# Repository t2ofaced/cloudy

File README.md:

# cloudy

A custom designed 60% Keyboard this keyboard is the first diy / electronic project i made from scratch, so idea was simple i wanted a keyboard so i desigined one now hopefully i can assemble it too so this keyboard use nice nano v2 clone pro micro nrf52840 development board as it give me freedom of wireless kayboard this keyboard also includes 1 enoder and 1 display and it is fully rgb thanks to SK6812MINI-E SMD leds

OnShape Link- https://cad.onshape.com/documents/02d1cc1f7ec3e59871e42e68/w/e27206701595b8be94d4fc96/e/017436c4cffd3847ba6185ca

---

## Schematics & Circuitry

Electornic part of this Proj is desigined in KiCad 10.0

<br>
this is main circuitry 

<br>

<br>
keyswitch matrix

<br>

<br>
rgb chain

---

## PCB Routing & 3D View

<br>
routed pcb

<br>

<br>
3d view

---

## CAD & Case Design

Mechanical part / CAD is desigined in 4 parts 2 each for Top plate and Base plate it is in 4 parts so  that it can be printed easily
Onshape - https://cad.onshape.com/documents/02d1cc1f7ec3e59871e42e68/w/e27206701595b8be94d4fc96/e/d50220b72c1b89afdf243eaf

<br>
keyboard with base plate

<br>

<br>
keyboard with top plate

---

## Final Assembly

<br>
fully assembled

# Bill of Materials

| Part Name | Quantity | Link | Info | Price (USD) |
|---|---|---|---|---|
| JLCPCB PCB Manufacturing & Shipping | 1 | [Link](https://jlcpcb.com/) | PCB | $35 |
| 0.96 inch OLED Display | 1 | [Link](https://robu.in/product/0-96-oled-display-module/) | OLED display | $2.35 |
| Tactile Switches | 7 sets | [Link](https://meckeys.com/shop/accessories/keyboard-accessories/key-switches/cherry-mx-rgb-switch/) | Switches | $26.3 |
| NiceNanoV2 | 1 | [Link](https://robu.in/product/pro-micro-nrf52840-development-board-compatible-with-nicenano-v2-0/) | MCU | i will buy my owm ($8.67) |
| 1N4148 Diodes | 70 | [Link](https://quartzcomponents.com/products/1n4148-zener-diodel) | Diodes | $2.22 |
| Custom Keycaps | 1 | [Link](https://curiositycaps.in/products/comic-mixed-light-cherry-1-7mm-thick-pbt-keycaps) | Keycaps | $24.35 |
| SK6812MINI-E SMD | 72 | [Link](https://www.etstore.in/products/e9974?variant=48993209319675&country=IN&currency=INR) | RGB LEDs | $9.73 |
| LiPo Battery | 1 | [Link](https://robu.in/product/400mah-pcm-protected-micro-li-po-battery/) | 3.7V 400mAh 1S | $2.32 |
| Disc Capacitor | 70 | [Link](https://robu.in/product/100nf-50v-disc-capacitor/) | 100nF 50V | $1 |
| Aluminum Electrolytic Capacitors | 5 | [Link](https://robu.in/product/ers1am471e12ot-aishi-470uf-10v-%C2%B120-plugind6-3xl12mm-aluminum-electrolytic-capacitors-leaded-rohs/?gad_source=1&gad_campaignid=17427802703&gbraid=0AAAAADvLFWeqncwaNG3o_D6R6zCnwtxQC) | ERS1AM471E12OT-AISHI 470uF 10V ±20% Plugin | $0.5 |
| Resistor 470 Ohms | 10 | [Link](https://www.ktron.in/product/resistor-470-ohms-0-25w-5-th/) | 470 Ohms 0.25W 5% TH | $0.2 |
| Male Connector | 3 | [Link](https://robu.in/product/ph-aw-2mm-2-pin-wafer-male-connector-through-hole-right-angle/) | PH-AW 2mm 2 pin | $0.2 |
| Rotary Encoder with Switch | 1 | [Link](https://robu.in/product/hongyan-ec11h-7ce20p1zd20-rotary-encoder-with-push-button-switch-vertical-plug-in-5-pin/) | EC11H 7CE20P1ZD20 5-Pin | $0.7 |
| Slide Switch | 5 | [Link](https://robu.in/product/slide-switch-ss-12d07-1p2t/) | SS-12D07 1P2T | $0.2 |
| Tactile Switch | 5 | [Link](https://robu.in/product/ws-a06-4-3-waterproof-tact-switch-4-pin6x6x4-3/) | 6x6x4.3mm 4 Pin | $0.2 |
| Stabilizers | 5 | [Link](https://stackskb.com/store/durock-clear-screw-in-stabilizers-v2) | 4+1 set | $16.93 |
| **TOTAL** | | | | **~$124** |

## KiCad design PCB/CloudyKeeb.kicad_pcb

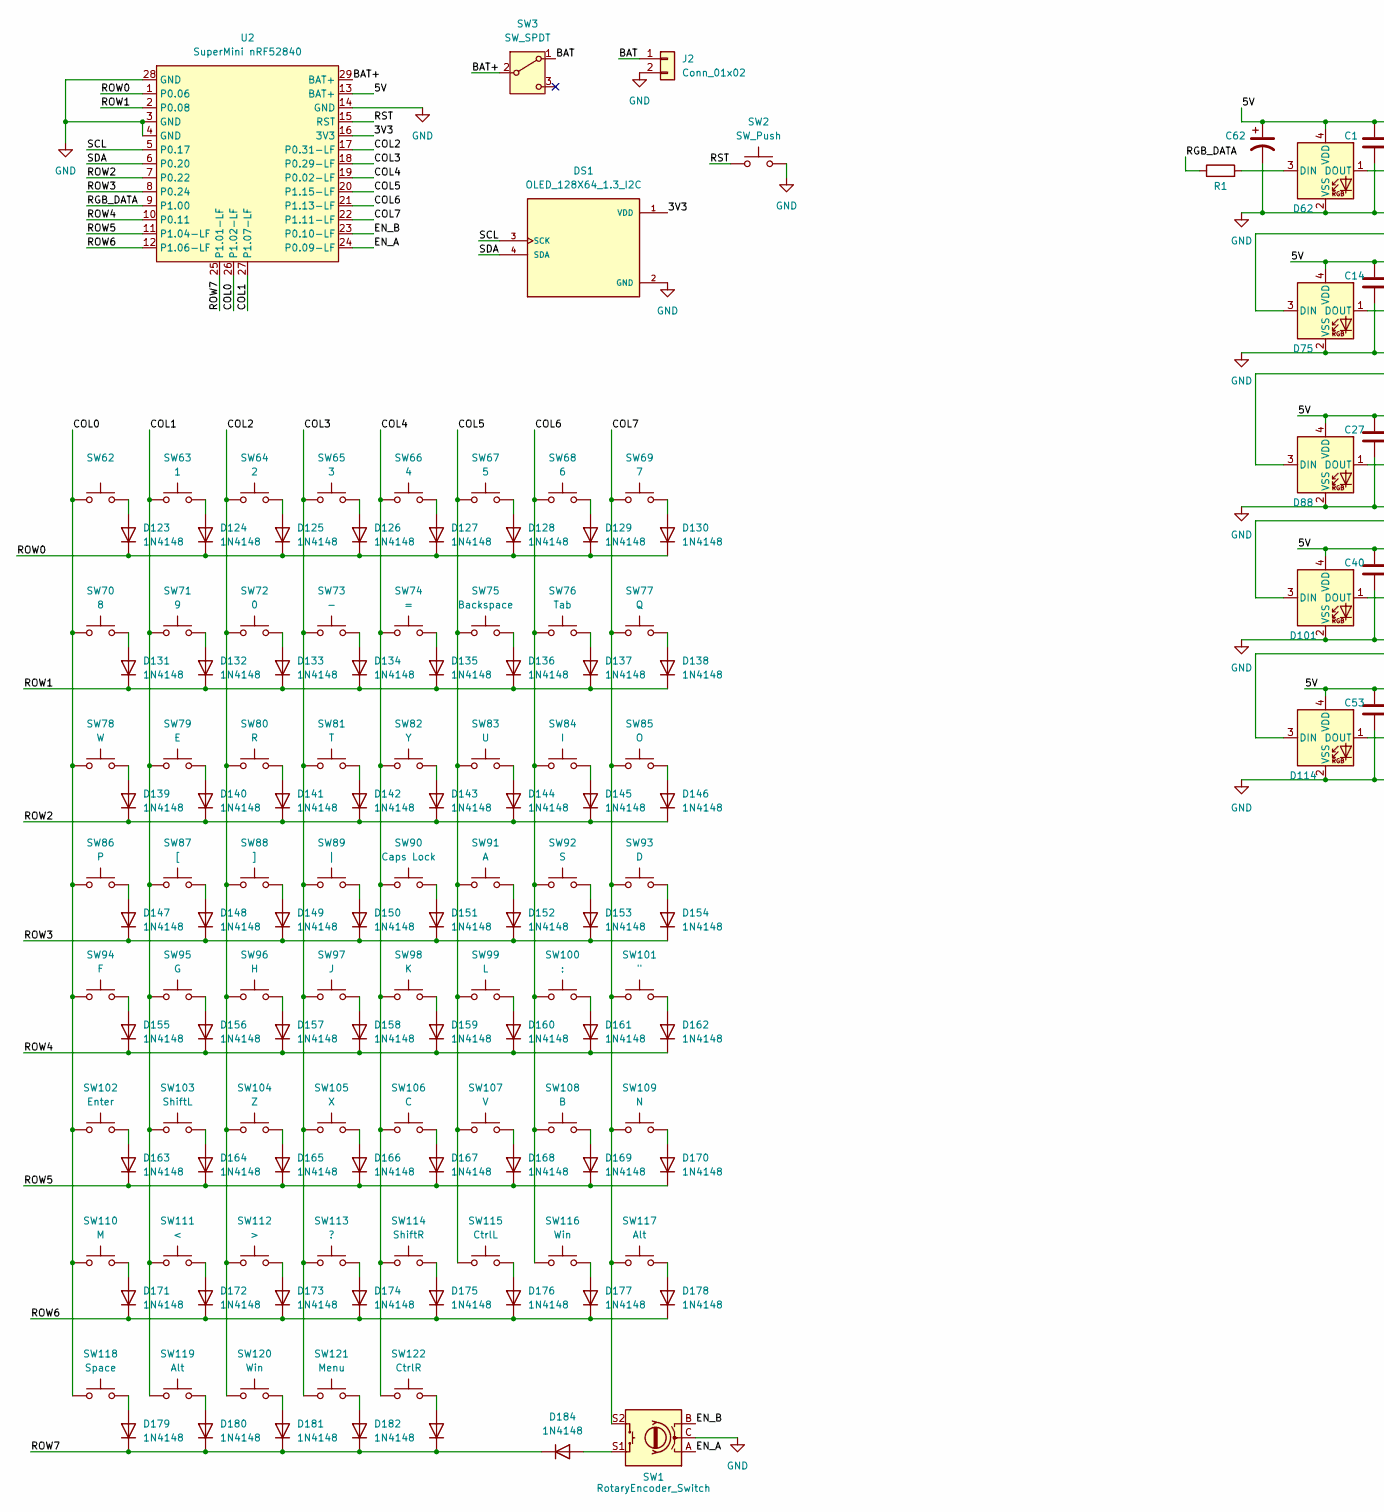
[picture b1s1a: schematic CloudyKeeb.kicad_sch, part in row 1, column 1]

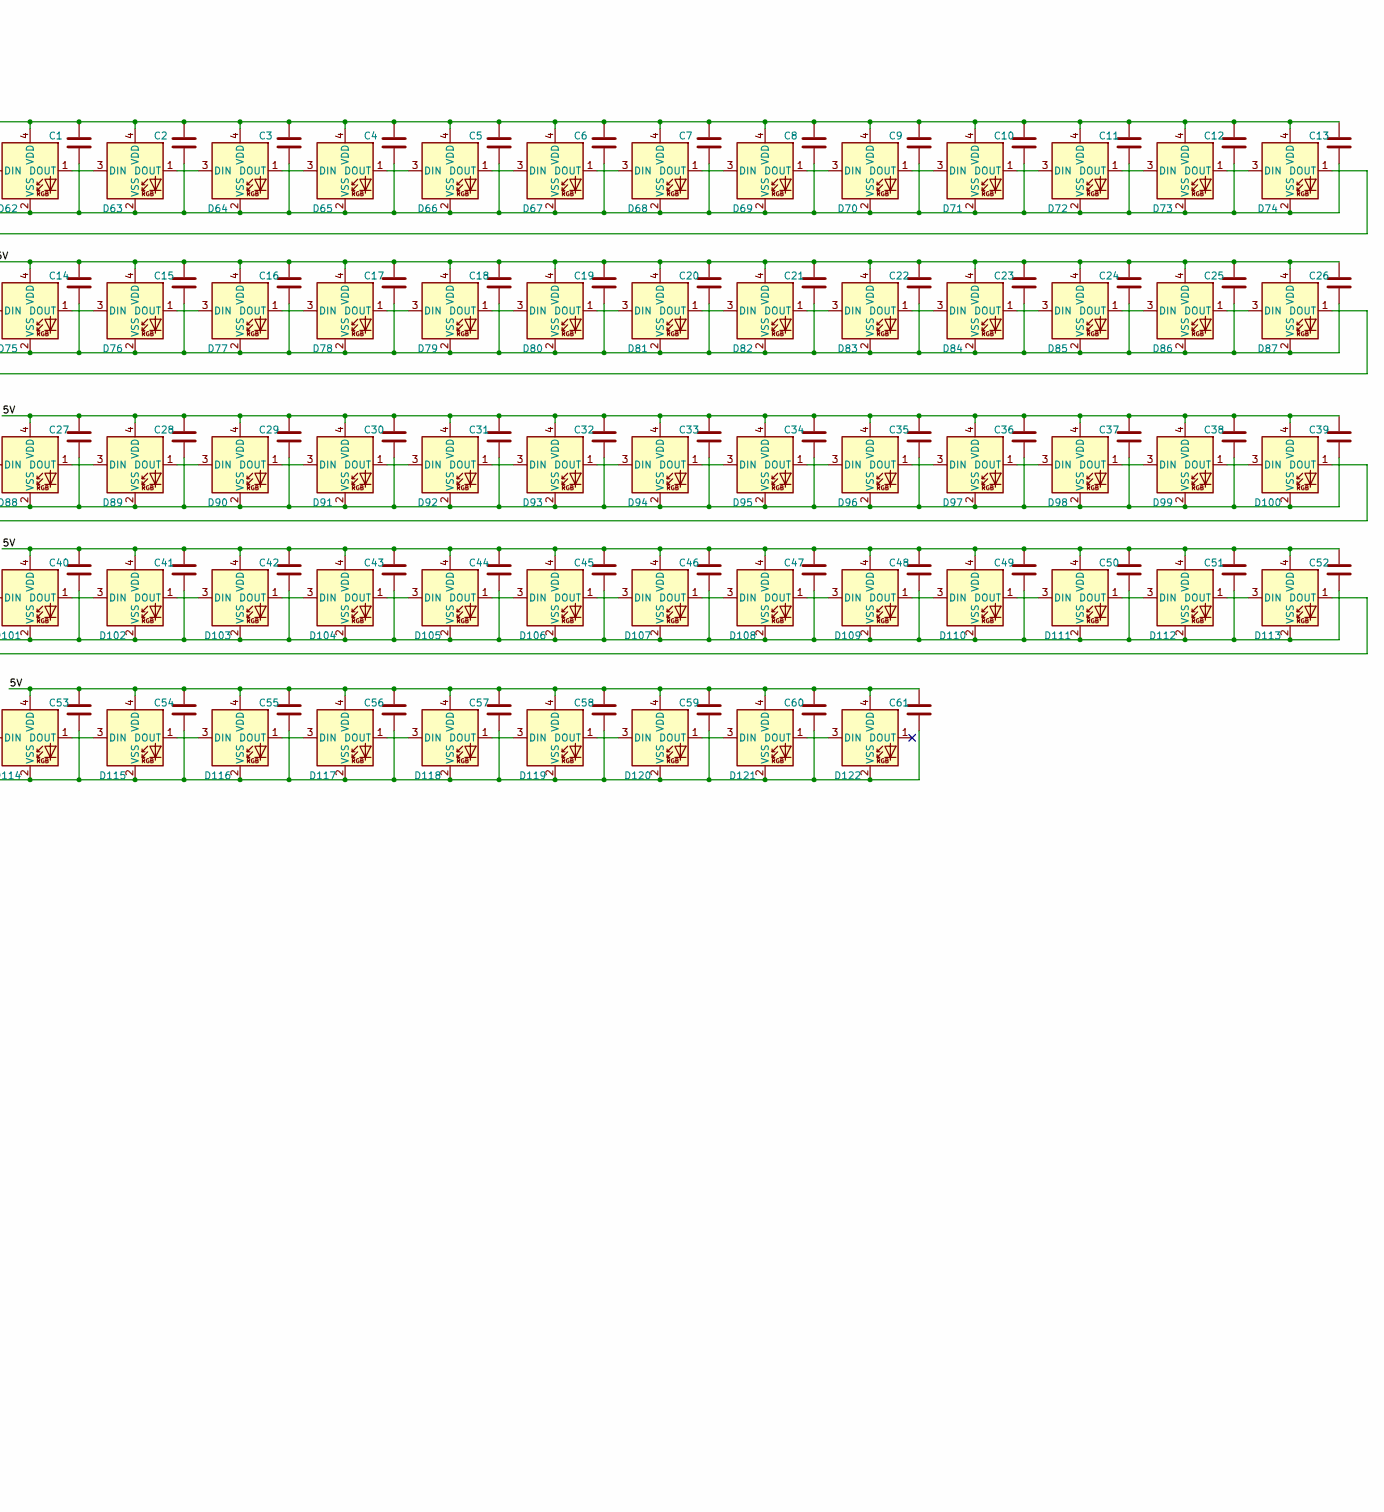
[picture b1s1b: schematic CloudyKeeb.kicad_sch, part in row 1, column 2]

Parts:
C1, C2, C3, C4, C5, C6, C7, C8, C9, C10, C11, C12, C13, C14, C15, C16, C17, C18, C19, C20, C21, C22, C23, C24, C25, C26, C27, C28, C29, C30, C31, C32, C33, C34, C35, C36, C37, C38, C39, C40, C41, C42, C43, C44, C45, C46, C47, C48, C49, C50, C51, C52, C53, C54, C55, C56, C57, C58, C59, C60, C61: C; C_Disc_D3.8mm_W2.6mm_P2.50mm
C62: C_Polarized_US; CP_Radial_D6.3mm_P2.50mm
D62, D63, D64, D65, D66, D67, D68, D69, D70, D71, D72, D73, D74, D75, D76, D77, D78, D79, D80, D81, D82, D83, D84, D85, D86, D87, D88, D89, D90, D91, D92, D93, D94, D95, D96, D97, D98, D99, D100, D101, D102, D103, D104, D105, D106, D107, D108, D109, D110, D111, D112, D113, D114, D115, D116, D117, D118, D119, D120, D121, D122: SK6812MINI; MX_SK6812MINI-E_REV
D123, D124, D125, D126, D127, D128, D129, D130, D131, D132, D133, D134, D135, D136, D137, D138, D139, D140, D141, D142, D143, D144, D145, D146, D147, D148, D149, D150, D151, D152, D153, D154, D155, D156, D157, D158, D159, D160, D161, D162, D163, D164, D165, D166, D167, D168, D169, D170, D171, D172, D173, D174, D175, D176, D177, D178, D179, D180, D181, D182, D183, D184: 1N4148; D_DO-35_SOD27_P7.62mm_Horizontal
DS1: OLED_128X64_1.3_I2C; LCD_OLED_128X64_1.3_I2C; PARTREV NA
J2: Conn_01x02; JST_PH_S2B-PH-K_1x02_P2.00mm_Horizontal
R1: Resistor; R_Axial_DIN0207_L6.3mm_D2.5mm_P10.16mm_Horizontal
SW1: RotaryEncoder_Switch; RotaryEncoder_Alps_EC11E-Switch_Vertical_H20mm_CircularMoun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
SW2: SW_Push; SW_PUSH_6mm_H4.3mm
SW3: SW_SPDT; SW_Slide-03_Wuerth-WS-SLTV_10x2.5x6.4_P2.54mm
SW62: MX-Solderable-1U
SW63: 1; MX-Solderable-1U
SW64: 2; MX-Solderable-1U
SW65: 3; MX-Solderable-1U
SW66: 4; MX-Solderable-1U
SW67: 5; MX-Solderable-1U
SW68: 6; MX-Solderable-1U
SW69: 7; MX-Solderable-1U
SW70: 8; MX-Solderable-1U
SW71: 9; MX-Solderable-1U
SW72: 0; MX-Solderable-1U
SW73: -; MX-Solderable-1U
SW74: =; MX-Solderable-1U
SW75: Backspace; MX-Solderable-2U
SW76: Tab; MX-Solderable-1.5U
SW77: Q; MX-Solderable-1U
SW78: W; MX-Solderable-1U
SW79: E; MX-Solderable-1U
SW80: R; MX-Solderable-1U
SW81: T; MX-Solderable-1U
SW82: Y; MX-Solderable-1U
SW83: U; MX-Solderable-1U
SW84: I; MX-Solderable-1U
SW85: O; MX-Solderable-1U
SW86: P; MX-Solderable-1U
SW87: [; MX-Solderable-1U
SW88: ]; MX-Solderable-1U
SW89: |; MX-Solderable-1.5U
SW90: Caps Lock; MX-Solderable-1.75U
SW91: A; MX-Solderable-1U
SW92: S; MX-Solderable-1U
SW93: D; MX-Solderable-1U
SW94: F; MX-Solderable-1U
SW95: G; MX-Solderable-1U
SW96: H; MX-Solderable-1U
SW97: J; MX-Solderable-1U
SW98: K; MX-Solderable-1U
SW99: L; MX-Solderable-1U
SW100: :; MX-Solderable-1U
SW101: "; MX-Solderable-1U
SW102: Enter; MX-Solderable-2.25U
SW103: ShiftL; MX-Solderable-2.25U
SW104: Z; MX-Solderable-1U
SW105: X; MX-Solderable-1U
SW106: C; MX-Solderable-1U
SW107: V; MX-Solderable-1U
SW108: B; MX-Solderable-1U
SW109: N; MX-Solderable-1U
SW110: M; MX-Solderable-1U
SW111: <; MX-Solderable-1U
SW112: >; MX-Solderable-1U
SW113: ?; MX-Solderable-1U
SW114: ShiftR; MX-Solderable-2.75U
SW115: CtrlL; MX-Solderable-1.25U
SW116, SW120: Win; MX-Solderable-1.25U
SW117, SW119: Alt; MX-Solderable-1.25U
SW118: Space; MX-Solderable-6.25U
SW121: Menu; MX-Solderable-1.25U
SW122: CtrlR; MX-Solderable-1.25U
U2: SuperMini nRF52840; SuperMini NRF52840

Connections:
/3V3: DS1.1 (VDD), U2.16 (3V3)
/5V: C1.1, C2.1, C3.1, C4.1, C5.1, C6.1, C7.1, C8.1, C9.1, C10.1, C11.1, C12.1, C13.1, C14.1, C15.1, C16.1, C17.1, C18.1, C19.1, C20.1, C21.1, C22.1, C23.1, C24.1, C25.1, C26.1, C27.1, C28.1, C29.1, C30.1, C31.1, C32.1, C33.1, C34.1, C35.1, C36.1, C37.1, C38.1, C39.1, C40.1, C41.1, C42.1, C43.1, C44.1, C45.1, C46.1, C47.1, C48.1, C49.1, C50.1, C51.1, C52.1, C53.1, C54.1, C55.1, C56.1, C57.1, C58.1, C59.1, C60.1, C61.1, C62.1, D62.4 (VDD), D63.4 (VDD), D64.4 (VDD), D65.4 (VDD), D66.4 (VDD), D67.4 (VDD), D68.4 (VDD), D69.4 (VDD), D70.4 (VDD), D71.4 (VDD), D72.4 (VDD), D73.4 (VDD), D74.4 (VDD), D75.4 (VDD), D76.4 (VDD), D77.4 (VDD), D78.4 (VDD), D79.4 (VDD), D80.4 (VDD), D81.4 (VDD), D82.4 (VDD), D83.4 (VDD), D84.4 (VDD), D85.4 (VDD), D86.4 (VDD), D87.4 (VDD), D88.4 (VDD), D89.4 (VDD), D90.4 (VDD), D91.4 (VDD), D92.4 (VDD), D93.4 (VDD), D94.4 (VDD), D95.4 (VDD), D96.4 (VDD), D97.4 (VDD), D98.4 (VDD), D99.4 (VDD), D100.4 (VDD), D101.4 (VDD), D102.4 (VDD), D103.4 (VDD), D104.4 (VDD), D105.4 (VDD), D106.4 (VDD), D107.4 (VDD), D108.4 (VDD), D109.4 (VDD), D110.4 (VDD), D111.4 (VDD), D112.4 (VDD), D113.4 (VDD), D114.4 (VDD), D115.4 (VDD), D116.4 (VDD), D117.4 (VDD), D118.4 (VDD), D119.4 (VDD), D120.4 (VDD), D121.4 (VDD), D122.4 (VDD), U2.13 (BAT+)
/BAT: J2.1, SW3.1 (A)
/BAT+: SW3.2 (B), U2.29 (BAT+)
/COL0: SW62.1, SW70.1, SW78.1, SW86.1, SW94.1, SW102.1, SW110.1, SW118.1, U2.26 (P1.02-LF)
/COL1: SW63.1, SW71.1, SW79.1, SW87.1, SW95.1, SW103.1, SW111.1, SW119.1, U2.27 (P1.07-LF)
/COL2: SW64.1, SW72.1, SW80.1, SW88.1, SW96.1, SW104.1, SW112.1, SW120.1, U2.17 (P0.31-LF)
/COL3: SW65.1, SW73.1, SW81.1, SW89.1, SW97.1, SW105.1, SW113.1, SW121.1, U2.18 (P0.29-LF)
/COL4: SW66.1, SW74.1, SW82.1, SW90.1, SW98.1, SW106.1, SW114.1, SW122.1, U2.19 (P0.02-LF)
/COL5: SW67.1, SW75.1, SW83.1, SW91.1, SW99.1, SW107.1, SW115.1, U2.20 (P1.15-LF)
/COL6: SW68.1, SW76.1, SW84.1, SW92.1, SW100.1, SW108.1, SW116.1, U2.21 (P1.13-LF)
/COL7: SW1.S2, SW69.1, SW77.1, SW85.1, SW93.1, SW101.1, SW109.1, SW117.1, U2.22 (P1.11-LF)
/EN_A: SW1.A, U2.24 (P0.09-LF)
/EN_B: SW1.B, U2.23 (P0.10-LF)
/RGB_DATA: R1.1, U2.9 (P1.00)
/ROW0: D123.1 (K), D124.1 (K), D125.1 (K), D126.1 (K), D127.1 (K), D128.1 (K), D129.1 (K), D130.1 (K), U2.1 (P0.06)
/ROW1: D131.1 (K), D132.1 (K), D133.1 (K), D134.1 (K), D135.1 (K), D136.1 (K), D137.1 (K), D138.1 (K), U2.2 (P0.08)
/ROW2: D139.1 (K), D140.1 (K), D141.1 (K), D142.1 (K), D143.1 (K), D144.1 (K), D145.1 (K), D146.1 (K), U2.7 (P0.22)
/ROW3: D147.1 (K), D148.1 (K), D149.1 (K), D150.1 (K), D151.1 (K), D152.1 (K), D153.1 (K), D154.1 (K), U2.8 (P0.24)
/ROW4: D155.1 (K), D156.1 (K), D157.1 (K), D158.1 (K), D159.1 (K), D160.1 (K), D161.1 (K), D162.1 (K), U2.10 (P0.11)
/ROW5: D163.1 (K), D164.1 (K), D165.1 (K), D166.1 (K), D167.1 (K), D168.1 (K), D169.1 (K), D170.1 (K), U2.11 (P1.04-LF)
/ROW6: D171.1 (K), D172.1 (K), D173.1 (K), D174.1 (K), D175.1 (K), D176.1 (K), D177.1 (K), D178.1 (K), U2.12 (P1.06-LF)
/ROW7: D179.1 (K), D180.1 (K), D181.1 (K), D182.1 (K), D183.1 (K), D184.1 (K), U2.25 (P1.01-LF)
/RST: SW2.1, U2.15 (RST)
/SCL: DS1.3 (SCK), U2.5 (P0.17)
/SDA: DS1.4 (SDA), U2.6 (P0.20)
GND: C1.2, C2.2, C3.2, C4.2, C5.2, C6.2, C7.2, C8.2, C9.2, C10.2, C11.2, C12.2, C13.2, C14.2, C15.2, C16.2, C17.2, C18.2, C19.2, C20.2, C21.2, C22.2, C23.2, C24.2, C25.2, C26.2, C27.2, C28.2, C29.2, C30.2, C31.2, C32.2, C33.2, C34.2, C35.2, C36.2, C37.2, C38.2, C39.2, C40.2, C41.2, C42.2, C43.2, C44.2, C45.2, C46.2, C47.2, C48.2, C49.2, C50.2, C51.2, C52.2, C53.2, C54.2, C55.2, C56.2, C57.2, C58.2, C59.2, C60.2, C61.2, C62.2, D62.2 (VSS), D63.2 (VSS), D64.2 (VSS), D65.2 (VSS), D66.2 (VSS), D67.2 (VSS), D68.2 (VSS), D69.2 (VSS), D70.2 (VSS), D71.2 (VSS), D72.2 (VSS), D73.2 (VSS), D74.2 (VSS), D75.2 (VSS), D76.2 (VSS), D77.2 (VSS), D78.2 (VSS), D79.2 (VSS), D80.2 (VSS), D81.2 (VSS), D82.2 (VSS), D83.2 (VSS), D84.2 (VSS), D85.2 (VSS), D86.2 (VSS), D87.2 (VSS), D88.2 (VSS), D89.2 (VSS), D90.2 (VSS), D91.2 (VSS), D92.2 (VSS), D93.2 (VSS), D94.2 (VSS), D95.2 (VSS), D96.2 (VSS), D97.2 (VSS), D98.2 (VSS), D99.2 (VSS), D100.2 (VSS), D101.2 (VSS), D102.2 (VSS), D103.2 (VSS), D104.2 (VSS), D105.2 (VSS), D106.2 (VSS), D107.2 (VSS), D108.2 (VSS), D109.2 (VSS), D110.2 (VSS), D111.2 (VSS), D112.2 (VSS), D113.2 (VSS), D114.2 (VSS), D115.2 (VSS), D116.2 (VSS), D117.2 (VSS), D118.2 (VSS), D119.2 (VSS), D120.2 (VSS), D121.2 (VSS), D122.2 (VSS), DS1.2 (GND), J2.2, SW1.C, SW2.2, U2.3 (GND), U2.4 (GND), U2.14 (GND), U2.28 (GND)
unnamed: D62.3 (DIN), R1.2
unnamed: D62.1 (DOUT), D63.3 (DIN)
unnamed: D63.1 (DOUT), D64.3 (DIN)
unnamed: D64.1 (DOUT), D65.3 (DIN)
unnamed: D65.1 (DOUT), D66.3 (DIN)
unnamed: D66.1 (DOUT), D67.3 (DIN)
unnamed: D67.1 (DOUT), D68.3 (DIN)
unnamed: D68.1 (DOUT), D69.3 (DIN)
unnamed: D69.1 (DOUT), D70.3 (DIN)
unnamed: D70.1 (DOUT), D71.3 (DIN)
unnamed: D71.1 (DOUT), D72.3 (DIN)
unnamed: D72.1 (DOUT), D73.3 (DIN)
unnamed: D73.1 (DOUT), D74.3 (DIN)
unnamed: D74.1 (DOUT), D75.3 (DIN)
unnamed: D75.1 (DOUT), D76.3 (DIN)
unnamed: D76.1 (DOUT), D77.3 (DIN)
unnamed: D77.1 (DOUT), D78.3 (DIN)
unnamed: D78.1 (DOUT), D79.3 (DIN)
unnamed: D79.1 (DOUT), D80.3 (DIN)
unnamed: D80.1 (DOUT), D81.3 (DIN)
unnamed: D81.1 (DOUT), D82.3 (DIN)
unnamed: D82.1 (DOUT), D83.3 (DIN)
unnamed: D83.1 (DOUT), D84.3 (DIN)
unnamed: D84.1 (DOUT), D85.3 (DIN)
unnamed: D85.1 (DOUT), D86.3 (DIN)
unnamed: D86.1 (DOUT), D87.3 (DIN)
unnamed: D87.1 (DOUT), D88.3 (DIN)
unnamed: D88.1 (DOUT), D89.3 (DIN)
unnamed: D89.1 (DOUT), D90.3 (DIN)
unnamed: D90.1 (DOUT), D91.3 (DIN)
unnamed: D91.1 (DOUT), D92.3 (DIN)
unnamed: D92.1 (DOUT), D93.3 (DIN)
unnamed: D93.1 (DOUT), D94.3 (DIN)
unnamed: D94.1 (DOUT), D95.3 (DIN)
unnamed: D95.1 (DOUT), D96.3 (DIN)
unnamed: D96.1 (DOUT), D97.3 (DIN)
unnamed: D97.1 (DOUT), D98.3 (DIN)
unnamed: D98.1 (DOUT), D99.3 (DIN)
unnamed: D99.1 (DOUT), D100.3 (DIN)
unnamed: D100.1 (DOUT), D101.3 (DIN)
unnamed: D101.1 (DOUT), D102.3 (DIN)
unnamed: D102.1 (DOUT), D103.3 (DIN)
unnamed: D103.1 (DOUT), D104.3 (DIN)
unnamed: D104.1 (DOUT), D105.3 (DIN)
unnamed: D105.1 (DOUT), D106.3 (DIN)
unnamed: D106.1 (DOUT), D107.3 (DIN)
unnamed: D107.1 (DOUT), D108.3 (DIN)
unnamed: D108.1 (DOUT), D109.3 (DIN)
unnamed: D109.1 (DOUT), D110.3 (DIN)
unnamed: D110.1 (DOUT), D111.3 (DIN)
unnamed: D111.1 (DOUT), D112.3 (DIN)
unnamed: D112.1 (DOUT), D113.3 (DIN)
unnamed: D113.1 (DOUT), D114.3 (DIN)
unnamed: D114.1 (DOUT), D115.3 (DIN)
unnamed: D115.1 (DOUT), D116.3 (DIN)
unnamed: D116.1 (DOUT), D117.3 (DIN)
unnamed: D117.1 (DOUT), D118.3 (DIN)
unnamed: D118.1 (DOUT), D119.3 (DIN)
unnamed: D119.1 (DOUT), D120.3 (DIN)
unnamed: D120.1 (DOUT), D121.3 (DIN)
unnamed: D121.1 (DOUT), D122.3 (DIN)
unnamed: D123.2 (A), SW62.2
unnamed: D124.2 (A), SW63.2
unnamed: D125.2 (A), SW64.2
unnamed: D126.2 (A), SW65.2
unnamed: D127.2 (A), SW66.2
unnamed: D128.2 (A), SW67.2
unnamed: D129.2 (A), SW68.2
unnamed: D130.2 (A), SW69.2
unnamed: D131.2 (A), SW70.2
unnamed: D132.2 (A), SW71.2
unnamed: D133.2 (A), SW72.2
unnamed: D134.2 (A), SW73.2
unnamed: D135.2 (A), SW74.2
unnamed: D136.2 (A), SW75.2
unnamed: D137.2 (A), SW76.2
unnamed: D138.2 (A), SW77.2
unnamed: D139.2 (A), SW78.2
unnamed: D140.2 (A), SW79.2
unnamed: D141.2 (A), SW80.2
unnamed: D142.2 (A), SW81.2
unnamed: D143.2 (A), SW82.2
unnamed: D144.2 (A), SW83.2
unnamed: D145.2 (A), SW84.2
unnamed: D146.2 (A), SW85.2
unnamed: D147.2 (A), SW86.2
unnamed: D148.2 (A), SW87.2
unnamed: D149.2 (A), SW88.2
unnamed: D150.2 (A), SW89.2
unnamed: D151.2 (A), SW90.2
unnamed: D152.2 (A), SW91.2
unnamed: D153.2 (A), SW92.2
unnamed: D154.2 (A), SW93.2
unnamed: D155.2 (A), SW94.2
unnamed: D156.2 (A), SW95.2
unnamed: D157.2 (A), SW96.2
unnamed: D158.2 (A), SW97.2
unnamed: D159.2 (A), SW98.2
unnamed: D160.2 (A), SW99.2
unnamed: D161.2 (A), SW100.2
unnamed: D162.2 (A), SW101.2
unnamed: D163.2 (A), SW102.2
unnamed: D164.2 (A), SW103.2
unnamed: D165.2 (A), SW104.2
unnamed: D166.2 (A), SW105.2
unnamed: D167.2 (A), SW106.2
unnamed: D168.2 (A), SW107.2
unnamed: D169.2 (A), SW108.2
unnamed: D170.2 (A), SW109.2
unnamed: D171.2 (A), SW110.2
unnamed: D172.2 (A), SW111.2
unnamed: D173.2 (A), SW112.2
unnamed: D174.2 (A), SW113.2
unnamed: D175.2 (A), SW114.2
unnamed: D176.2 (A), SW115.2
unnamed: D177.2 (A), SW116.2
unnamed: D178.2 (A), SW117.2
unnamed: D179.2 (A), SW118.2
unnamed: D180.2 (A), SW119.2
unnamed: D181.2 (A), SW120.2
unnamed: D182.2 (A), SW121.2
unnamed: D183.2 (A), SW122.2
unnamed: D184.2 (A), SW1.S1

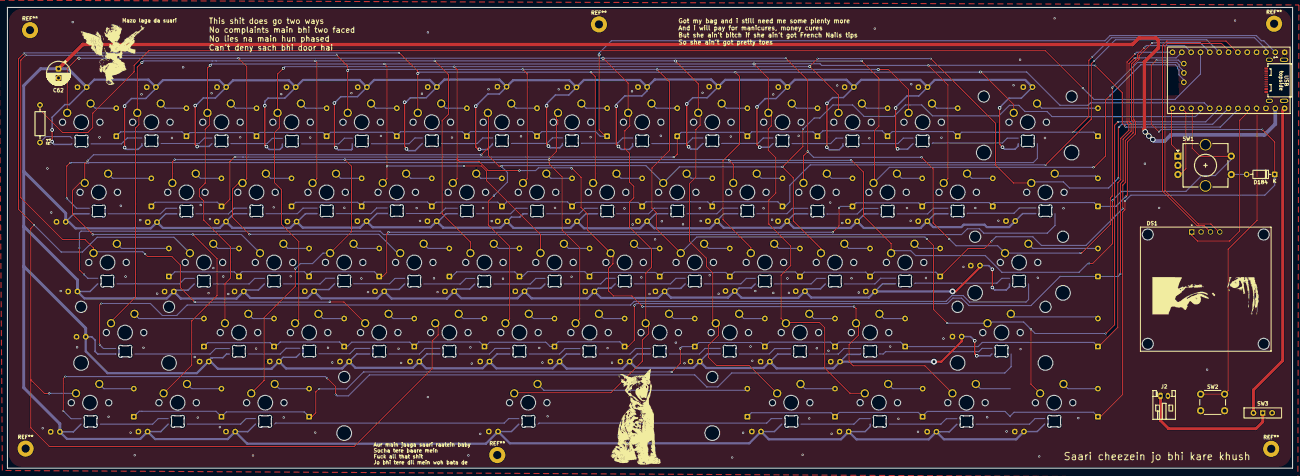
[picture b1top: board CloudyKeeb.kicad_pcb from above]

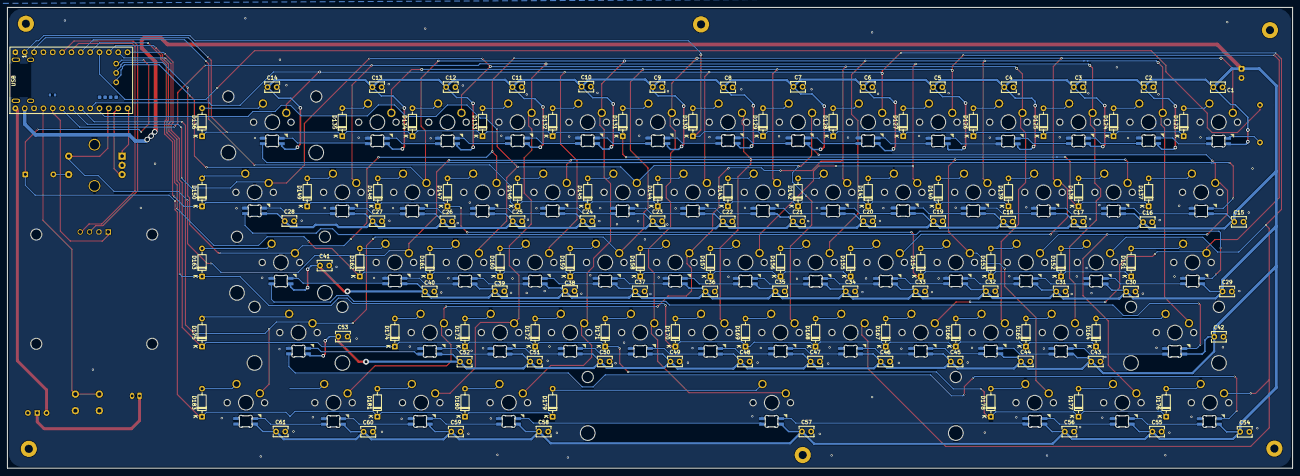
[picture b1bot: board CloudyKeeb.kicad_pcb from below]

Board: 2 copper layers, 349.1 x 125.2 mm, 252 parts (121 on the bottom side), 149 nets.

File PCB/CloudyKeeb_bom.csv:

Designator,Footprint,Quantity,Value,LCSC Part #
"C1, C10, C11, C12, C13, C14, C15, C16, C17, C18, C19, C2, C20, C21, C22, C23, C24, C25, C26, C27, C28, C29, C3, C30, C31, C32, C33, C34, C35, C36, C37, C38, C39, C4, C40, C41, C42, C43, C44, C45, C46, C47, C48, C49, C5, C50, C51, C52, C53, C54, C55, C56, C57, C58, C59, C6, C60, C61, C7, C8, C9",C_Disc_D3.8mm_W2.6mm_P2.50mm,61,C,
C62,CP_Radial_D6.3mm_P2.50mm,1,C_Polarized_US,
"D100, D101, D102, D103, D104, D105, D106, D107, D108, D109, D110, D111, D112, D113, D114, D115, D116, D117, D118, D119, D120, D121, D122, D62, D63, D64, D65, D66, D67, D68, D69, D70, D71, D72, D73, D74, D75, D76, D77, D78, D79, D80, D81, D82, D83, D84, D85, D86, D87, D88, D89, D90, D91, D92, D93, D94, D95, D96, D97, D98, D99",MX_SK6812MINI-E_REV,61,SK6812MINI,
"D123, D124, D125, D126, D127, D128, D129, D130, D131, D132, D133, D134, D135, D136, D137, D138, D139, D140, D141, D142, D143, D144, D145, D146, D147, D148, D149, D150, D151, D152, D153, D154, D155, D156, D157, D158, D159, D160, D161, D162, D163, D164, D165, D166, D167, D168, D169, D170, D171, D172, D173, D174, D175, D176, D177, D178, D179, D180, D181, D182, D183, D184",D_DO-35_SOD27_P7.62mm_Horizontal,62,1N4148,
DS1,LCD_OLED_128X64_1.3_I2C,1,OLED_128X64_1.3_I2C,
J2,JST_PH_S2B-PH-K_1x02_P2.00mm_Horizontal,1,Conn_01x02,
R1,R_Axial_DIN0207_L6.3mm_D2.5mm_P10.16mm_Horizontal,1,Resistor,
SW1,RotaryEncoder_Alps_EC11E-Switch_Vertical_H20mm_CircularMountingHoles,1,RotaryEncoder_Switch,
SW100,MX-Solderable-1U,1,:,
SW101,MX-Solderable-1U,1,"""",
SW102,MX-Solderable-2.25U,1,Enter,
SW103,MX-Solderable-2.25U,1,ShiftL,
SW104,MX-Solderable-1U,1,Z,
SW105,MX-Solderable-1U,1,X,
SW106,MX-Solderable-1U,1,C,
SW107,MX-Solderable-1U,1,V,
SW108,MX-Solderable-1U,1,B,
SW109,MX-Solderable-1U,1,N,
SW110,MX-Solderable-1U,1,M,
SW111,MX-Solderable-1U,1,<,
SW112,MX-Solderable-1U,1,>,
SW113,MX-Solderable-1U,1,?,
SW114,MX-Solderable-2.75U,1,ShiftR,
SW115,MX-Solderable-1.25U,1,CtrlL,
"SW116, SW120",MX-Solderable-1.25U,2,Win,
"SW117, SW119",MX-Solderable-1.25U,2,Alt,
SW118,MX-Solderable-6.25U,1,Space,
SW121,MX-Solderable-1.25U,1,Menu,
SW122,MX-Solderable-1.25U,1,CtrlR,
SW2,SW_PUSH_6mm_H4.3mm,1,SW_Push,
SW3,SW_Slide-03_Wuerth-WS-SLTV_10x2.5x6.4_P2.54mm,1,SW_SPDT,
SW62,MX-Solderable-1U,1,~,
SW63,MX-Solderable-1U,1,1,
SW64,MX-Solderable-1U,1,2,
SW65,MX-Solderable-1U,1,3,
SW66,MX-Solderable-1U,1,4,
SW67,MX-Solderable-1U,1,5,
SW68,MX-Solderable-1U,1,6,
SW69,MX-Solderable-1U,1,7,
SW70,MX-Solderable-1U,1,8,
SW71,MX-Solderable-1U,1,9,
SW72,MX-Solderable-1U,1,0,
SW73,MX-Solderable-1U,1,-,
SW74,MX-Solderable-1U,1,=,
SW75,MX-Solderable-2U,1,Backspace,
SW76,MX-Solderable-1.5U,1,Tab,
SW77,MX-Solderable-1U,1,Q,
SW78,MX-Solderable-1U,1,W,
SW79,MX-Solderable-1U,1,E,
SW80,MX-Solderable-1U,1,R,
SW81,MX-Solderable-1U,1,T,
SW82,MX-Solderable-1U,1,Y,
SW83,MX-Solderable-1U,1,U,
SW84,MX-Solderable-1U,1,I,
SW85,MX-Solderable-1U,1,O,
SW86,MX-Solderable-1U,1,P,
SW87,MX-Solderable-1U,1,[,
SW88,MX-Solderable-1U,1,],
SW89,MX-Solderable-1.5U,1,|,
SW90,MX-Solderable-1.75U,1,Caps Lock,
SW91,MX-Solderable-1U,1,A,
SW92,MX-Solderable-1U,1,S,
SW93,MX-Solderable-1U,1,D,
SW94,MX-Solderable-1U,1,F,
SW95,MX-Solderable-1U,1,G,
SW96,MX-Solderable-1U,1,H,
SW97,MX-Solderable-1U,1,J,
SW98,MX-Solderable-1U,1,K,
SW99,MX-Solderable-1U,1,L,
